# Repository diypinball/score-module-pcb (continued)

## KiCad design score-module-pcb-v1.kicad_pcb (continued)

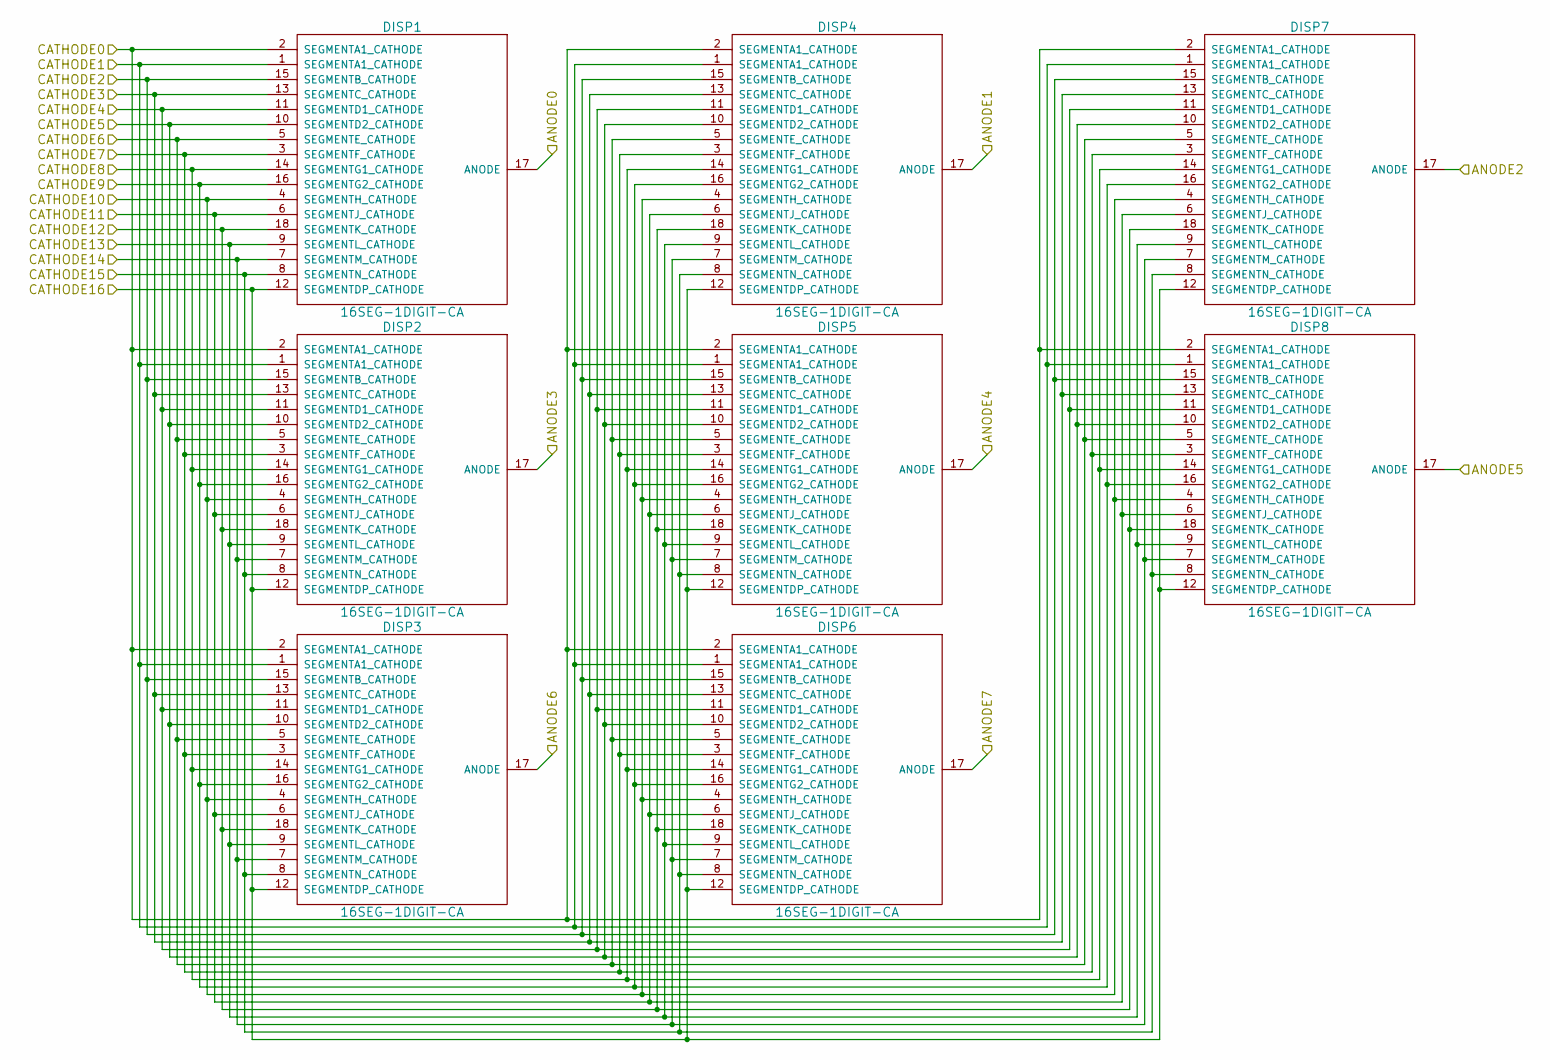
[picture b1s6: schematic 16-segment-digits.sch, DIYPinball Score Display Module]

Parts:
DISP1, DISP2, DISP3, DISP4, DISP5, DISP6, DISP7, DISP8: 16SEG-1DIGIT-CA; LCSA-8018

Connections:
/16-Segment Digits/ANODE0: DISP1.17 (ANODE); also elsewhere on the board
/16-Segment Digits/ANODE1: DISP4.17 (ANODE); also elsewhere on the board
/16-Segment Digits/ANODE2: DISP7.17 (ANODE); also elsewhere on the board
/16-Segment Digits/ANODE3: DISP2.17 (ANODE); also elsewhere on the board
/16-Segment Digits/ANODE4: DISP5.17 (ANODE); also elsewhere on the board
/16-Segment Digits/ANODE5: DISP8.17 (ANODE); also elsewhere on the board
/16-Segment Digits/ANODE6: DISP3.17 (ANODE); also elsewhere on the board
/16-Segment Digits/ANODE7: DISP6.17 (ANODE); also elsewhere on the board
/16-Segment Digits/CATHODE0: DISP1.2 (SEGMENTA1_CATHODE), DISP2.2 (SEGMENTA1_CATHODE), DISP3.2 (SEGMENTA1_CATHODE), DISP4.2 (SEGMENTA1_CATHODE), DISP5.2 (SEGMENTA1_CATHODE), DISP6.2 (SEGMENTA1_CATHODE), DISP7.2 (SEGMENTA1_CATHODE), DISP8.2 (SEGMENTA1_CATHODE); also elsewhere on the board
/16-Segment Digits/CATHODE1: DISP1.1 (SEGMENTA1_CATHODE), DISP2.1 (SEGMENTA1_CATHODE), DISP3.1 (SEGMENTA1_CATHODE), DISP4.1 (SEGMENTA1_CATHODE), DISP5.1 (SEGMENTA1_CATHODE), DISP6.1 (SEGMENTA1_CATHODE), DISP7.1 (SEGMENTA1_CATHODE), DISP8.1 (SEGMENTA1_CATHODE); also elsewhere on the board
/16-Segment Digits/CATHODE2: DISP1.15 (SEGMENTB_CATHODE), DISP2.15 (SEGMENTB_CATHODE), DISP3.15 (SEGMENTB_CATHODE), DISP4.15 (SEGMENTB_CATHODE), DISP5.15 (SEGMENTB_CATHODE), DISP6.15 (SEGMENTB_CATHODE), DISP7.15 (SEGMENTB_CATHODE), DISP8.15 (SEGMENTB_CATHODE); also elsewhere on the board
/16-Segment Digits/CATHODE3: DISP1.13 (SEGMENTC_CATHODE), DISP2.13 (SEGMENTC_CATHODE), DISP3.13 (SEGMENTC_CATHODE), DISP4.13 (SEGMENTC_CATHODE), DISP5.13 (SEGMENTC_CATHODE), DISP6.13 (SEGMENTC_CATHODE), DISP7.13 (SEGMENTC_CATHODE), DISP8.13 (SEGMENTC_CATHODE); also elsewhere on the board
/16-Segment Digits/CATHODE4: DISP1.11 (SEGMENTD1_CATHODE), DISP2.11 (SEGMENTD1_CATHODE), DISP3.11 (SEGMENTD1_CATHODE), DISP4.11 (SEGMENTD1_CATHODE), DISP5.11 (SEGMENTD1_CATHODE), DISP6.11 (SEGMENTD1_CATHODE), DISP7.11 (SEGMENTD1_CATHODE), DISP8.11 (SEGMENTD1_CATHODE); also elsewhere on the board
/16-Segment Digits/CATHODE5: DISP1.10 (SEGMENTD2_CATHODE), DISP2.10 (SEGMENTD2_CATHODE), DISP3.10 (SEGMENTD2_CATHODE), DISP4.10 (SEGMENTD2_CATHODE), DISP5.10 (SEGMENTD2_CATHODE), DISP6.10 (SEGMENTD2_CATHODE), DISP7.10 (SEGMENTD2_CATHODE), DISP8.10 (SEGMENTD2_CATHODE); also elsewhere on the board
/16-Segment Digits/CATHODE6: DISP1.5 (SEGMENTE_CATHODE), DISP2.5 (SEGMENTE_CATHODE), DISP3.5 (SEGMENTE_CATHODE), DISP4.5 (SEGMENTE_CATHODE), DISP5.5 (SEGMENTE_CATHODE), DISP6.5 (SEGMENTE_CATHODE), DISP7.5 (SEGMENTE_CATHODE), DISP8.5 (SEGMENTE_CATHODE); also elsewhere on the board
/16-Segment Digits/CATHODE7: DISP1.3 (SEGMENTF_CATHODE), DISP2.3 (SEGMENTF_CATHODE), DISP3.3 (SEGMENTF_CATHODE), DISP4.3 (SEGMENTF_CATHODE), DISP5.3 (SEGMENTF_CATHODE), DISP6.3 (SEGMENTF_CATHODE), DISP7.3 (SEGMENTF_CATHODE), DISP8.3 (SEGMENTF_CATHODE); also elsewhere on the board
/16-Segment Digits/CATHODE8: DISP1.14 (SEGMENTG1_CATHODE), DISP2.14 (SEGMENTG1_CATHODE), DISP3.14 (SEGMENTG1_CATHODE), DISP4.14 (SEGMENTG1_CATHODE), DISP5.14 (SEGMENTG1_CATHODE), DISP6.14 (SEGMENTG1_CATHODE), DISP7.14 (SEGMENTG1_CATHODE), DISP8.14 (SEGMENTG1_CATHODE); also elsewhere on the board
/16-Segment Digits/CATHODE9: DISP1.16 (SEGMENTG2_CATHODE), DISP2.16 (SEGMENTG2_CATHODE), DISP3.16 (SEGMENTG2_CATHODE), DISP4.16 (SEGMENTG2_CATHODE), DISP5.16 (SEGMENTG2_CATHODE), DISP6.16 (SEGMENTG2_CATHODE), DISP7.16 (SEGMENTG2_CATHODE), DISP8.16 (SEGMENTG2_CATHODE); also elsewhere on the board
/16-Segment Digits/CATHODE10: DISP1.4 (SEGMENTH_CATHODE), DISP2.4 (SEGMENTH_CATHODE), DISP3.4 (SEGMENTH_CATHODE), DISP4.4 (SEGMENTH_CATHODE), DISP5.4 (SEGMENTH_CATHODE), DISP6.4 (SEGMENTH_CATHODE), DISP7.4 (SEGMENTH_CATHODE), DISP8.4 (SEGMENTH_CATHODE); also elsewhere on the board
/16-Segment Digits/CATHODE11: DISP1.6 (SEGMENTJ_CATHODE), DISP2.6 (SEGMENTJ_CATHODE), DISP3.6 (SEGMENTJ_CATHODE), DISP4.6 (SEGMENTJ_CATHODE), DISP5.6 (SEGMENTJ_CATHODE), DISP6.6 (SEGMENTJ_CATHODE), DISP7.6 (SEGMENTJ_CATHODE), DISP8.6 (SEGMENTJ_CATHODE); also elsewhere on the board
/16-Segment Digits/CATHODE12: DISP1.18 (SEGMENTK_CATHODE), DISP2.18 (SEGMENTK_CATHODE), DISP3.18 (SEGMENTK_CATHODE), DISP4.18 (SEGMENTK_CATHODE), DISP5.18 (SEGMENTK_CATHODE), DISP6.18 (SEGMENTK_CATHODE), DISP7.18 (SEGMENTK_CATHODE), DISP8.18 (SEGMENTK_CATHODE); also elsewhere on the board
/16-Segment Digits/CATHODE13: DISP1.9 (SEGMENTL_CATHODE), DISP2.9 (SEGMENTL_CATHODE), DISP3.9 (SEGMENTL_CATHODE), DISP4.9 (SEGMENTL_CATHODE), DISP5.9 (SEGMENTL_CATHODE), DISP6.9 (SEGMENTL_CATHODE), DISP7.9 (SEGMENTL_CATHODE), DISP8.9 (SEGMENTL_CATHODE); also elsewhere on the board
/16-Segment Digits/CATHODE14: DISP1.7 (SEGMENTM_CATHODE), DISP2.7 (SEGMENTM_CATHODE), DISP3.7 (SEGMENTM_CATHODE), DISP4.7 (SEGMENTM_CATHODE), DISP5.7 (SEGMENTM_CATHODE), DISP6.7 (SEGMENTM_CATHODE), DISP7.7 (SEGMENTM_CATHODE), DISP8.7 (SEGMENTM_CATHODE); also elsewhere on the board
/16-Segment Digits/CATHODE15: DISP1.8 (SEGMENTN_CATHODE), DISP2.8 (SEGMENTN_CATHODE), DISP3.8 (SEGMENTN_CATHODE), DISP4.8 (SEGMENTN_CATHODE), DISP5.8 (SEGMENTN_CATHODE), DISP6.8 (SEGMENTN_CATHODE), DISP7.8 (SEGMENTN_CATHODE), DISP8.8 (SEGMENTN_CATHODE); also elsewhere on the board
/16-Segment Digits/CATHODE16: DISP1.12 (SEGMENTDP_CATHODE), DISP2.12 (SEGMENTDP_CATHODE), DISP3.12 (SEGMENTDP_CATHODE), DISP4.12 (SEGMENTDP_CATHODE), DISP5.12 (SEGMENTDP_CATHODE), DISP6.12 (SEGMENTDP_CATHODE), DISP7.12 (SEGMENTDP_CATHODE), DISP8.12 (SEGMENTDP_CATHODE); also elsewhere on the board

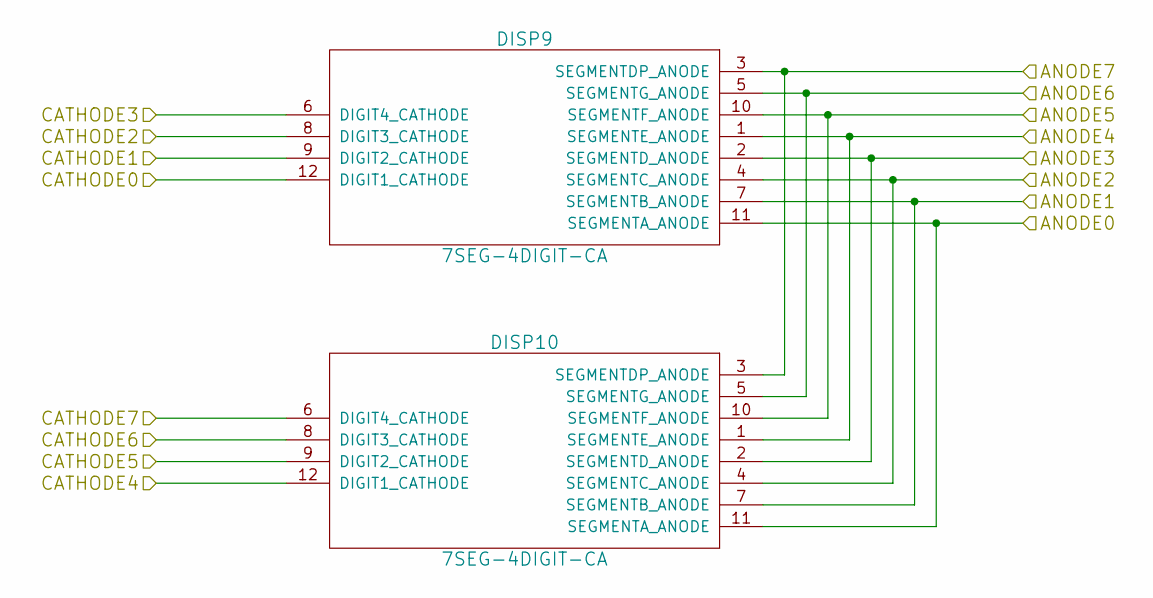
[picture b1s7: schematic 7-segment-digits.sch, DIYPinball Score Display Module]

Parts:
DISP9, DISP10: 7SEG-4DIGIT-CA; ATA8041

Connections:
/16-Segment Digits/ANODE0: DISP9.11 (SEGMENTA_ANODE), DISP10.11 (SEGMENTA_ANODE); also elsewhere on the board
/16-Segment Digits/ANODE1: DISP9.7 (SEGMENTB_ANODE), DISP10.7 (SEGMENTB_ANODE); also elsewhere on the board
/16-Segment Digits/ANODE2: DISP9.4 (SEGMENTC_ANODE), DISP10.4 (SEGMENTC_ANODE); also elsewhere on the board
/16-Segment Digits/ANODE3: DISP9.2 (SEGMENTD_ANODE), DISP10.2 (SEGMENTD_ANODE); also elsewhere on the board
/16-Segment Digits/ANODE4: DISP9.1 (SEGMENTE_ANODE), DISP10.1 (SEGMENTE_ANODE); also elsewhere on the board
/16-Segment Digits/ANODE5: DISP9.10 (SEGMENTF_ANODE), DISP10.10 (SEGMENTF_ANODE); also elsewhere on the board
/16-Segment Digits/ANODE6: DISP9.5 (SEGMENTG_ANODE), DISP10.5 (SEGMENTG_ANODE); also elsewhere on the board
/16-Segment Digits/ANODE7: DISP9.3 (SEGMENTDP_ANODE), DISP10.3 (SEGMENTDP_ANODE); also elsewhere on the board
/16-Segment Digits/CATHODE0: DISP9.12 (DIGIT1_CATHODE); also elsewhere on the board
/16-Segment Digits/CATHODE1: DISP9.9 (DIGIT2_CATHODE); also elsewhere on the board
/16-Segment Digits/CATHODE2: DISP9.8 (DIGIT3_CATHODE); also elsewhere on the board
/16-Segment Digits/CATHODE3: DISP9.6 (DIGIT4_CATHODE); also elsewhere on the board
/16-Segment Digits/CATHODE4: DISP10.12 (DIGIT1_CATHODE); also elsewhere on the board
/16-Segment Digits/CATHODE5: DISP10.9 (DIGIT2_CATHODE); also elsewhere on the board
/16-Segment Digits/CATHODE6: DISP10.8 (DIGIT3_CATHODE); also elsewhere on the board
/16-Segment Digits/CATHODE7: DISP10.6 (DIGIT4_CATHODE); also elsewhere on the board

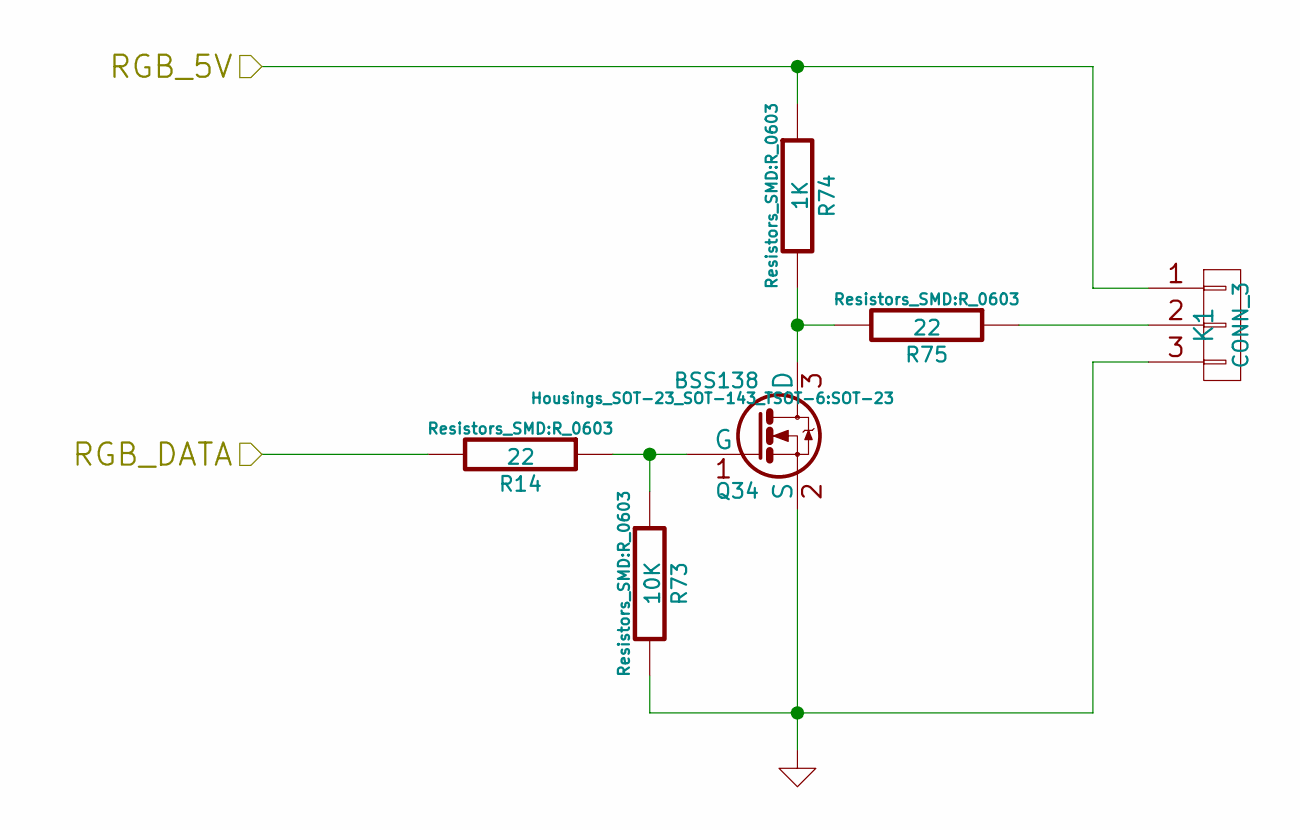
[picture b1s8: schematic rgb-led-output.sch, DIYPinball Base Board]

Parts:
K1: CONN_3; Socket_MOLEX-KK-RM2-54mm_Lock_3pin_straight
Q34: BSS138; SOT-23
R14, R75: 22; R_0603
R73: 10K; R_0603
R74: 1K; R_0603

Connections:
+5V: K1.1, R74.1; also elsewhere on the board
/RGB Output/RGB_DATA: R14.2; also elsewhere on the board
GND: K1.3, Q34.2 (S), R73.2; also elsewhere on the board
unnamed: K1.2, R75.1
unnamed: Q34.1 (G), R14.1, R73.1
unnamed: Q34.3 (D), R74.2, R75.2

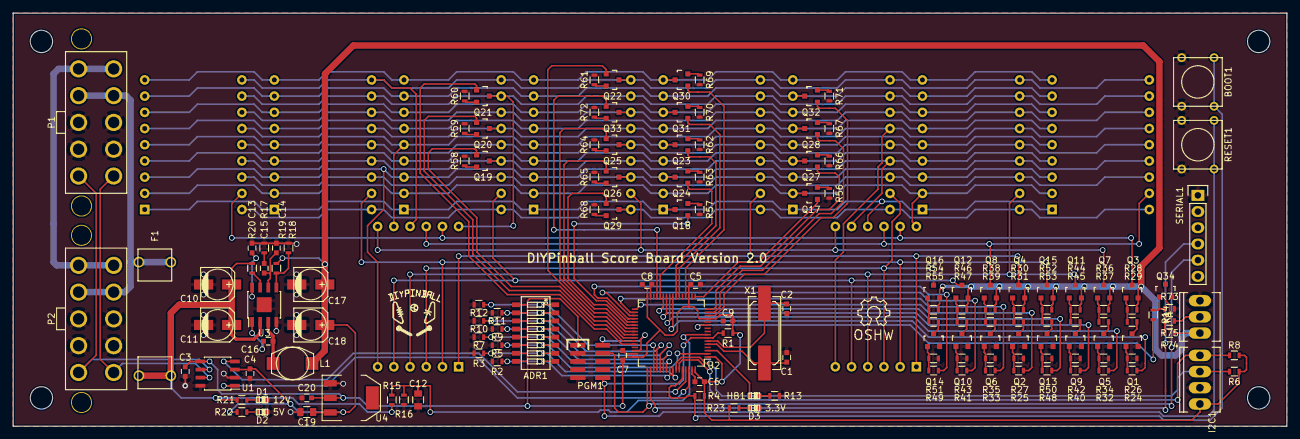
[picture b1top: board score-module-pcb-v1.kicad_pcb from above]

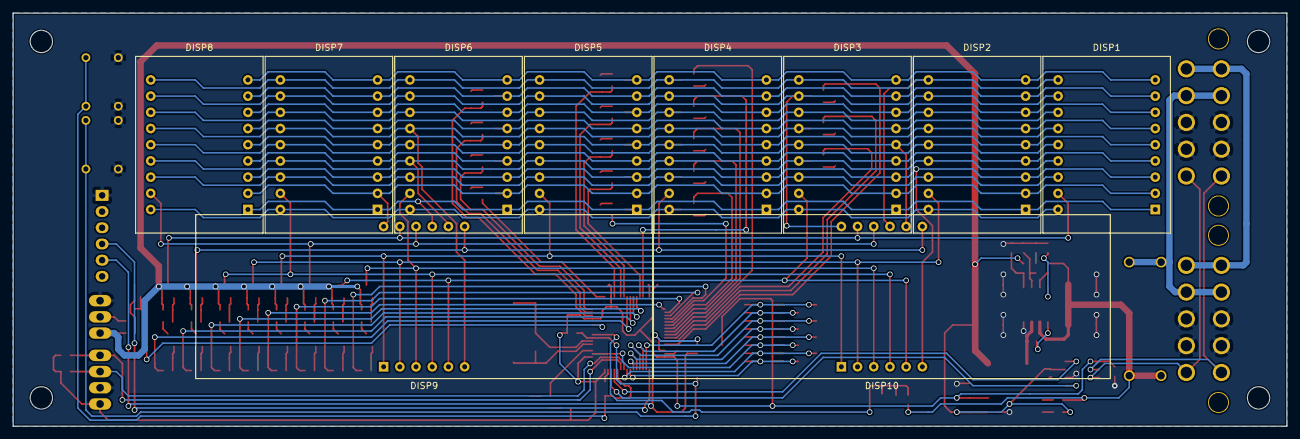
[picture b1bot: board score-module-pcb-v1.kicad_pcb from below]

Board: 4 copper layers, 199.7 x 64.8 mm, 159 parts (10 on the bottom side), 135 nets.

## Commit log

2015-08-05 Initial commit. Schematic not yet complete.
2015-10-14 I think the layout is finished now. I'll check again after I sleep.
2015-10-15 Added square pads to LED displays for Pin 1. Reflowed ground floods to update them.
2016-09-09 Adding RGB LED driver
